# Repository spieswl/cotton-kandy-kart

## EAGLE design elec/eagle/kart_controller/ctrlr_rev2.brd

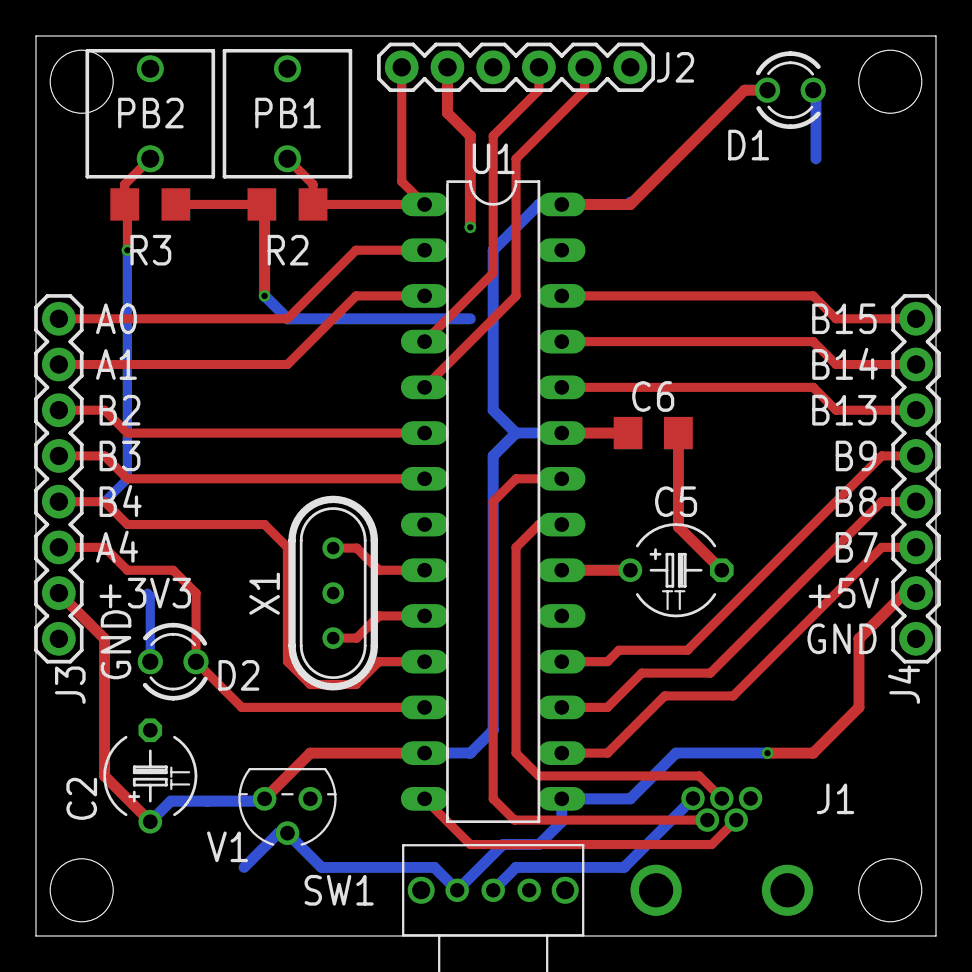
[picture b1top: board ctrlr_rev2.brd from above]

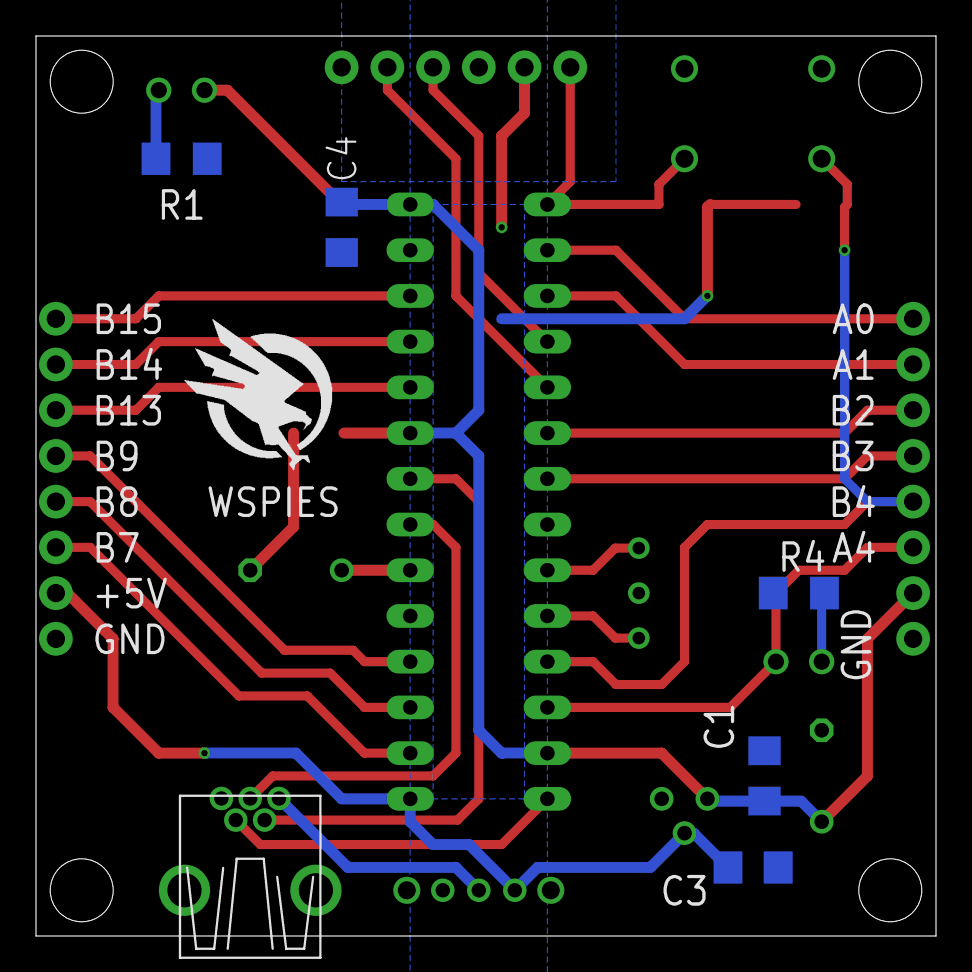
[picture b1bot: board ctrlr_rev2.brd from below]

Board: 2 copper layers, 50.0 x 50.0 mm, 22 parts (5 on the bottom side), 27 nets.

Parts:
C1, C3, C4, C6: 0.1uF; C1206
C2, C5: 10uF; TAP5-50
D1: LED-RED; LED-3MM-V
D2: LED-GREEN; LED-3MM-V
J1: USB-MINI-B; USB-MB-TO
J2: HEADER-6; CONN_1X06
J3, J4: HEADER-8; CONN_1X08
PB1, PB2: EVQ-11A07K; PCPIN-2
R1, R4: 330; R1206
R2, R3: 10.0k; R1206
SW1: 1825232-1; PCPIN-3SS
U1: PIC32MX250F128B; DIP28-3
V1: MCP1702; TO-92
X1: CSTLS8M00G53; RAD-3-2.5

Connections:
+3V3: C1.1, C2.+, C4.1, C6.1, D1.A, J2.2, J3.2, R2.2, R3.2, U1.13, U1.23, U1.28, V1.3
+5V: C3.1, J4.2, SW1.1, U1.15, V1.2
A0: J3.8, U1.2
A1: J3.7, U1.3
A4: D2.A, J3.3, U1.12
B2: J3.6, U1.6
B3: J3.5, U1.7
B4: J3.4, PB2.1, R3.1, U1.11
B7: J4.3, U1.16
B8: J4.4, U1.17
B9: J4.5, U1.18
B13: J4.6, U1.24
B14: J4.7, U1.25
B15: J4.8, U1.26
D+: J1.D+, U1.21
D-: J1.D-, U1.22
GND: C1.2, C2.-, C3.2, C4.2, C5.-, C6.2, J1.GND, J2.3, J3.1, J4.1, PB1.2, PB2.2, R1.1, R4.1, U1.8, U1.19, U1.27, V1.1, X1.2
MCLR: J2.1, PB1.1, R2.1, U1.1
unnamed: D2.K, R4.2
unnamed: D1.K, R1.2
unnamed: J1.VBUS, SW1.2
unnamed: C5.+, U1.20
OSC1: U1.9, X1.1
OSC2: U1.10, X1.3
PGC: J2.5, U1.5
PGD: J2.4, U1.4
USBID: J1.ID, U1.14

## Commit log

2018-04-09 Getting HW1 folder set up; added 'code_template.txt'.
2018-04-09 Added MPLAB IDE project and introduced template code. Also some initial screencaps of power supply circuit ripple (and suppression).
2018-04-09 Code compiles and loads to PIC32 microcontroller; LED 2 is working.
    Now to add the looping code.
2018-04-09 Fully debugged and tested (with what little code we have there). Final images to support are yet to come.
2018-04-09 Added images for HW1, tweaked gitignore file.
2018-04-12 Schematic and board layout complete, may need further refinement for header locations.
2018-04-12 Moved the Eagle project to its own folder; Nick doesn't have HW3 stuff up yet so looks like this will be in its own area for the moment.
2018-04-13 Added Gerbers for HW3, tweaked board layout and saved as Rev2. Not happy on the hole sizing on the layout (thanks Eagle) so I may come back and make those larger for standard standoffs.
2018-04-13 Changed the mounting hole size to be 3.5mm diameter, to handle standard post holes from something like a #4 standoff.
2018-04-18 HW4 started, have SPI communication to the MCP4912 working, verified by using SPI interface to command MCP4912 to output 1.65 V on DAC Channel A and 3.0 V on DAC Channel B.
2018-04-18 Refactored a bunch of stuff, HW4 is now complete, renamed directories to be a little clearer when looking through the files.
2018-04-24 HW5 complete, added I2C code and schematics for I2C circuit in HW5 folder.
2018-04-25 HW6 in progress, LCD_drawChar code works on the LCD display, which is wired up and operational.
2018-04-25 HW6 complete, updated assignment to draw FPS graph and progress bar. Plus added a schematic showing the connections in the included Eagle project.
2018-04-30 HW7 Checkpoint : IMU interface is working correctly, X-Axis bars are working correctly (could use some polishing however). Need to extend IMU measurement scale to Y-Axis.
2018-05-01 HW7 checkpoint : Both Y-axis and X-axis bars are working properly, fixed some bugs, added a little bit more logging to the main program.
2018-05-01 HW8 (HW1 redux) completed and tested on the PIC32.
2018-05-07 Initial pass at CDC programming, sample code is set up and working properly. Moving onto the bulk of HW9 coding.
2018-05-07 Adding IMU code to HW9, not happy with the polling frequency of the IMU (essentially just unsure of whether or not I should have the IMU read in a different area than message write, seems like I shou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
2018-05-08 Finished up HW9, still not too happy with where I am doing the reading (mostly because the state machine we were given still seems nebulous to me). Code works, though.
2018-05-08 Tweaked HW9 code (after conferring w/ the Wiznitzers on state machine machinations). Should be at 100 Hz for everything now.
2018-05-10 Added filter functions to a DSP header, need to add weights to FIR filter and add main-line code to leverage those filtering capabilities to tasks.
2018-05-10 Initial coding for DSP operations are complete, testing and plotting of data still needs to be done.
2018-05-10 HW10 is complete and tested, fixed some bugs with each of the filters, performance seems really good! Also synthesized the HW11 project for HID mouse control.
2018-05-10 HW11 complete; mouse works, tested it just a little bit ago. Needed to remove the (-1) being multiplied by the values for it to not have "inverted X, inverted Y" functionality. Also used X and Z acce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
    I could absolutely tweak with the signed short values to reduce how quickly my mouse moves around on Ubuntu linux, but I'll just leave it as is for now.
2018-05-10 Added the 9 "zeroes" and 1 true accelerometer value code, so its not blasting the IMU values every time the code sends an HID report.
2018-05-17 Android app programmed for HW12, just copy the HelloWorld_HW12 folder to your Android Studio projects directory if you want to make any other changes.
2018-05-20 Completed HW13 project with the Camera app.
2018-05-23 PIC code now working correctly for HW14, added Android Studio project for the second part of the exercise.
2018-05-23 Android app updated and complete; tested it with my OnePlus One. Added the USB functionality to the app, as well. HW14 is essentially complete.
2018-05-28 Added pictures of my living hinge box and the 3D-printed wheel designs.
2018-06-11 Work-in-Progress on robot code for final project (PI control nearly complete, Android app needs to be ported over).
2018-06-12 Added a complete version of the Android app, needs some tweaks and testing, but otherwise should be in good shape. The PIC code was also updated. Still needs to have the PI controller code added, how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
2018-06-12 Fixed some bugs in the Android app, tested it and it works with the PIC.
2018-06-13 Updated and completed the Android app, tested and working on the robot.
2018-06-13 Updated controller and ran the whole system together. Needs some improvements to the controller, but otherwise, the design is sound and working.
2018-06-14 Moved in my electrical schematics and added some pictures showing the final design.
2018-06-18 Added mechanical detail drawings. No model files included (check Onshape for those files).
2018-06-18 Reconfigured old ME433 repository into a dedicated repo (while preserving the commit history) for the aptly-named Cotton Kandy robotic kart.
2018-07-07 Added PDFs of both the schematic and the PCB layout, for preview purposes.
2019-10-03 Added BSD-3-c license
2020-08-21 * Cleaned up detail drawings in mechanical section * Resized docs images to be smaller
